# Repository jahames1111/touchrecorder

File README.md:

# Simple voice recorder - ESP32-based

### Why
Making a durable, easy-to-use voice recorder for my mom's classroom with a cool UI screen. No loose wires.

### Parts
* Ideaspark ESP32 with 1.14" ST7789 TFT
* INMP441 I2S Mic Breakout
* SPI Micro SD Module + Card
* Big home limit switches
* Sockets, resistors, caps

### Plan
1. Route SPI/I2S once jlcpcb kicad board gets here
2. Plug modules into 2.54mm sockets
3. Solder switches via wires
4. Do code stuff in arduino IDE

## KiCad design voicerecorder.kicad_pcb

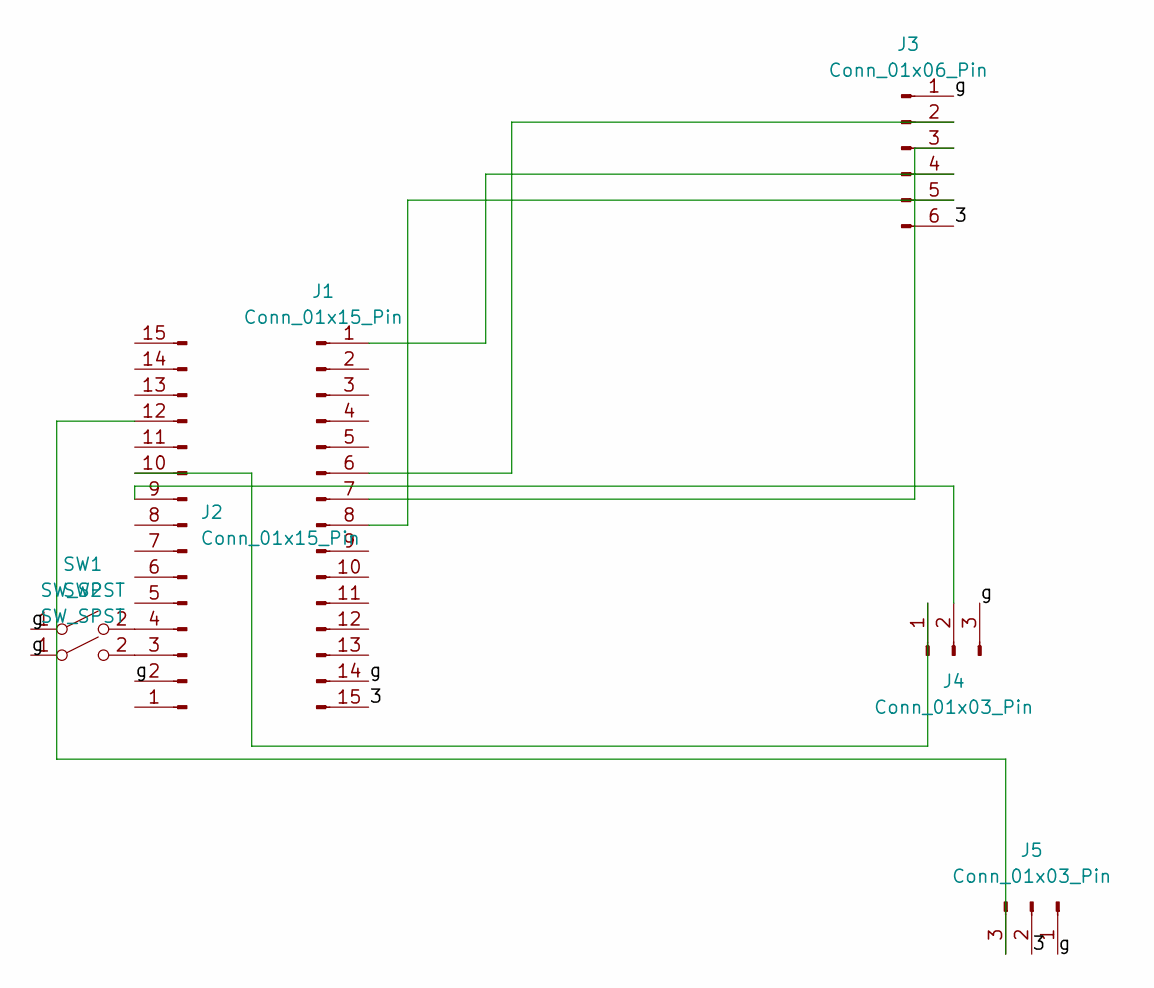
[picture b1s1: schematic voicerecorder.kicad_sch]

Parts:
J1, J2: Conn_01x15_Pin; PinSocket_1x15_P2.54mm_Vertical
J3: Conn_01x06_Pin; PinSocket_1x06_P2.54mm_Vertical
J4, J5: Conn_01x03_Pin; PinSocket_1x03_P2.54mm_Vertical
SW1, SW2: SW_SPST; SW_PUSH_6mm_H5mm

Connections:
/3: J1.15, J3.6, J5.2
/g: J1.14, J2.2, J3.1, J4.3, J5.1, SW1.1 (A), SW2.1 (A)
unnamed: J1.1, J3.4
unnamed: J1.6, J3.2
unnamed: J1.7, J3.3
unnamed: J1.8, J3.5
unnamed: J2.3, SW2.2 (B)
unnamed: J2.4, SW1.2 (B)
unnamed: J2.9, J4.2
unnamed: J2.10, J4.1
unnamed: J2.12, J5.3

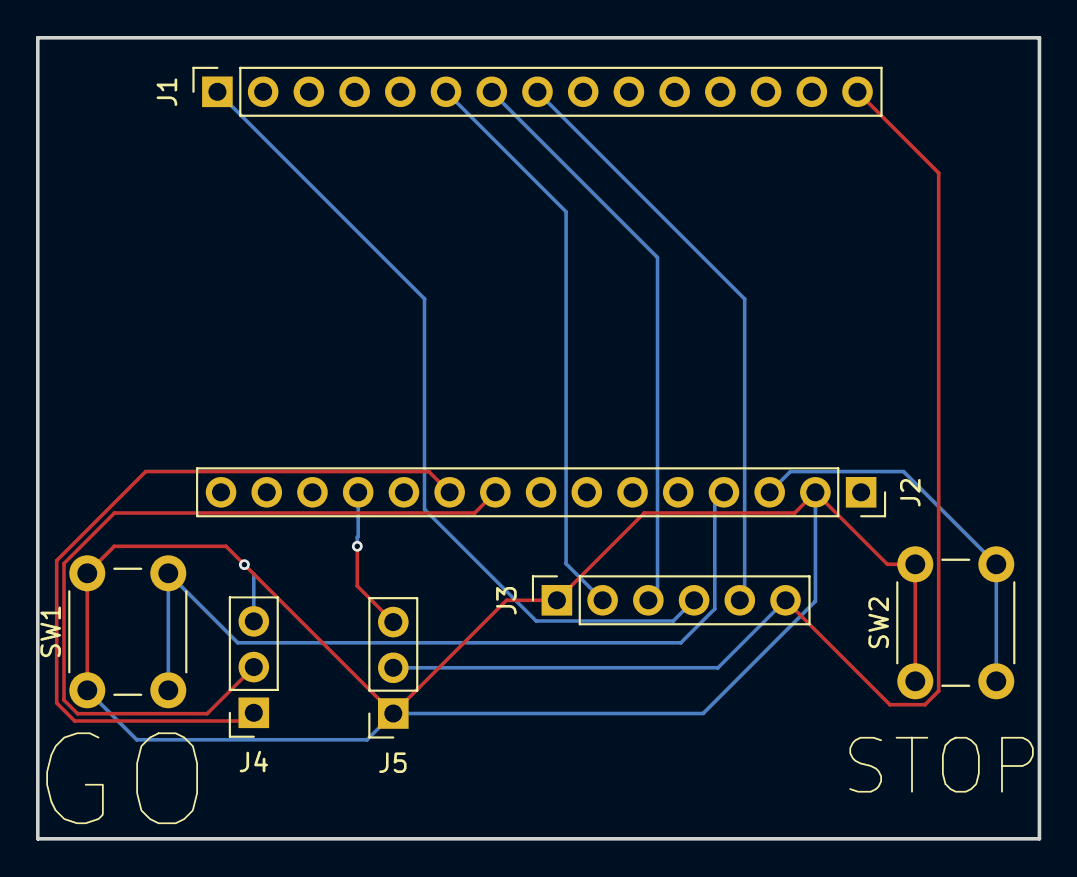
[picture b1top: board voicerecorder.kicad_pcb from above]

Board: 2 copper layers, 55.6 x 44.5 mm, 7 parts (0 on the bottom side), 11 nets.
